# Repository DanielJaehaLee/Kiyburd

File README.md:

# Kiyburd

**Split 40% ortholinear diode-less mechanical keyboard**

Kiyburd is a split keyboard built around a 44-key ortholinear grid, direct-pin wiring (no diode matrix), and a pair of Raspberry Pi Picos talking over TRRS. The goal is a compact, stabilizer-free board that is easier to wire and firmware-tune than a conventional matrix keyboard, without giving up QMK features.

| | |
|---|---|
| **Form factor** | Split 40% · 22 keys per half · 44 keys total |
| **Grid** | Ortholinear 1u keys · no stabilized keys |
| **Scanning** | Direct GPIO (diode-less / matrix-less) |
| **MCU** | Raspberry Pi Pico (RP2040) × 2 |
| **Inter-half link** | TRRS (PJ-320A) · full-duplex USART |
| **Firmware** | [QMK](https://qmk.fm/) |
| **PCB** | Reversible |
| **Status** | PCB designed and ordered · QMK port working · case and Vial still open |

---

## Why this layout

Most 40% boards still carry a row/column matrix, diodes, and at least a few 2u keys that need stabilizers. Kiyburd drops those on purpose:

- **Split 40%** keeps the hands apart and the keymap small enough that layers do the work of a full-size board.
- **Ortholinear 1u grid** removes stagger and every stabilizer. Every switch is the same Cherry MX footprint.
- **Direct wiring** maps each switch to its own RP2040 GPIO. No diodes, no shared rows/columns, no ghosting to design around.
- **Reversible PCB** means one Gerber set builds both halves.

The default firmware keymap is QWERTY with three extra layers (function keys, numbers/arrows, symbols/nav). The files under `keyboard layout/` also document an experimental layered map with Hangul legends.

---

## Repository layout

```
Kiyburd/
├── Firmware/                 QMK keyboard definition
│   ├── config.h              RP2040 bootloader + USART pins
│   ├── info.json             Matrix pins, USB IDs, layout geometry
│   ├── kiyburd.h             LAYOUT() macro
│   ├── rules.mk              RP2040 + split keyboard
│   └── keymaps/default/      QWERTY + Lower / Raise / Raise2
├── PCB/Kiyburd/              KiCad 7/8 project
│   ├── Kiyburd.kicad_sch
│   ├── Kiyburd.kicad_pcb
│   └── production/           BOM, CPL, Gerbers (Kiyburd.zip)
└── keyboard layout/          Keyboard Layout Editor JSON / SVG / PNG
```

---

## Hardware

### Bill of materials (per half)

| Qty | Part | Notes |
|----:|------|--------|
| 1 | Raspberry Pi Pico (RP2040) | Socket or solder; USB-C or Micro-USB depending on Pico revision |
| 1 | PJ-320A TRRS jack | Inter-half serial + GND |
| 22 | Cherry MX compatible switches | 5-pin preferred; footprint is `SW_Cherry_MX_1.00u_PCB_reversible` |
| 22 | 1u keycaps | No 2u / no stabs |
| 1 | TRRS cable | Tip-ring-ring-sleeve; not a TRS headphone cable |

Build two halves. The PCB is reversible: the Pico and TRRS footprints are placed so the same board works as left or right.

### Direct-pin map

Each switch is wired to one GPIO. Left and right halves mirror each other.

**Left half**

| Row | Col 0 | Col 1 | Col 2 | Col 3 | Col 4 | Col 5 |
|-----|-------|-------|-------|-------|-------|-------|
| 0 | GP7 | GP6 | GP5 | GP4 | GP3 | GP2 |
| 1 | GP13 | GP12 | GP11 | GP10 | GP9 | GP8 |
| 2 | GP22 | GP26 | GP27 | GP28 | GP15 | GP14 |
| 3 | GP18 | — | — | GP19 | GP20 | GP21 |

**Right half**

| Row | Col 0 | Col 1 | Col 2 | Col 3 | Col 4 | Col 5 |
|-----|-------|-------|-------|-------|-------|-------|
| 0 | GP2 | GP3 | GP4 | GP5 | GP6 | GP7 |
| 1 | GP8 | GP9 | GP10 | GP11 | GP12 | GP13 |
| 2 | GP14 | GP15 | GP28 | GP27 | GP26 | GP22 |
| 3 | GP21 | GP20 | GP19 | — | — | GP18 |

Split serial is full-duplex USART on the Pico's vendor serial driver:

| Signal | Pin |
|--------|-----|
| TX | GP1 |
| RX | GP0 |

Handedness defaults to left-as-master. Uncomment `#define MASTER_RIGHT` in `Firmware/config.h` if the right half should own USB.

### Ordering the PCB

Gerbers and assembly files live in `PCB/Kiyburd/production/`:

- `Kiyburd.zip` — Gerber/drill package
- `bom.csv` — bill of materials
- `positions.csv` — pick-and-place
- `designators.csv` / `netlist.ipc`

Open `PCB/Kiyburd/Kiyburd.kicad_pro` in KiCad to edit the board before re-exporting.

---

## Firmware

Firmware is a QMK keyboard named `kiyburd`. It targets the RP2040 bootloader and enables Bootmagic, extra keys, mouse keys, and NKRO.

### Features (`info.json`)

- `bootmagic`, `extrakey`, `mousekey`, `nkro`
- USB VID `0xFEED` / PID `0x0000` / device version `1.0.0` (change these before sharing boards)
- Double-tap reset on the Pico (`RP2040_BOOTLOADER_DOUBLE_TAP_RESET`, 1000 ms window)

### Build

After [setting up QMK](https://docs.qmk.fm/#/newbs):

```sh
# drop this folder into qmk_firmware/keyboards/kiyburd
make kiyburd:default
make kiyburd:default:flash
```

Or with the QMK CLI:

```sh
qmk compile -kb kiyburd -km default
qmk flash -kb kiyburd -km default
```

Copy the contents of `Firmware/` to `qmk_firmware/keyboards/kiyburd/` so the make target matches the documented name.

### Enter the bootloader

1. **Bootmagic** — hold the matrix `(0, 0)` key (Tab on the default map) and plug in USB.
2. **Double-tap reset** — tap the Pico RESET button twice within one second.
3. **Bootsel** — hold BOOTSEL on the Pico, plug in USB, then drop the `.uf2` onto the RPI-RP2 drive.

### Default keymap

Four layers. Modifiers stay on the home row edges; `MO(1)` / `MO(2)` / `MO(3)` sit on the inner thumb cluster.

```
Layer 0 — QWERTY
,-----------------------------------------.     ,-----------------------------------------.
| Tab  |  Q   |  W   |  E   |  R   |  T   |     |  Y   |  U   |  I   |  O   |  P   | Bksp |
| Ctrl |  A   |  S   |  D   |  F   |  G   |     |  H   |  J   |  K   |  L   |  ;   |  '   |
| Shift|  Z   |  X   |  C   |  V   |  B   |     |  N   |  M   |  ,   |  .   |  /   |  \   |
| Alt  |           | GUI |Lower| Space |     |Raise|Raise2| RAlt |           | Enter|
`-----------------------------------------'     `-----------------------------------------'

Layer 1 — Lower          function keys on the right hand
Layer 2 — Raise          1–0, ` - = [ ], arrows
Layer 3 — Raise2         shifted symbols, Home / Ins / Del / End
```

Edit `Firmware/keymaps/default/keymap.c` to change layers. The Keyboard Layout Editor sources in `keyboard layout/` are a good place to mock a new map before touching C.

---

## Build notes

1. Fabricate two PCBs from `PCB/Kiyburd/production/Kiyburd.zip`.
2. Solder the Pico and TRRS jack. Because the footprints are reversible, decide handedness before soldering if you are not using sockets.
3. Solder 22 MX switches per half. There are no diodes.
4. Flash QMK to both Picos.
5. Join the halves with a TRRS cable. Plug USB into the master half only.
6. Confirm every key in a matrix tester, then cap the board.

There is no case in this repo yet. The housing work is still an open milestone (FreeCAD).

---

## Project status

| Area | State |
|------|--------|
| KiCad proficiency / PCB design | Done |
| PCB ordered | Done |
| Direct-switch and split-link electrical design | Done |
| QMK port | Done |
| Vial | Not started |
| Case / FreeCAD | Not started |

---

## References

Designs that informed the brief:

- [Budgy](https://github.com/doesntfazer/Budgy) — Pico-powered split, diode-less
- [Cantor](https://github.com/diepala/cantor) — 42-key diode-less split
- [Chiron](https://github.com/qmk/qmk_firmware/blob/master/keyboards/handwired/chiron/keymaps/default/keymap.c)
- [Dactyl Manuform](https://github.com/qmk/qmk_firmware/tree/master/keyboards/handwired/dactyl_manuform)

Docs:

- [QMK getting started](https://docs.qmk.fm/#/newbs)
- [QMK split keyboard](https://docs.qmk.fm/#/feature_split_keyboard)
- [RP2040 on QMK](https://docs.qmk.fm/#/platformdev_rp2040)

---

## License

Firmware sources carry `SPDX-License-Identifier: GPL-2.0-or-later` (QMK). Hardware files in `PCB/` do not declare a license yet — treat them as all-rights-reserved unless a license is added.

Maintainer: [DanielJaehaLee](https://github.com/DanielJaehaLee)

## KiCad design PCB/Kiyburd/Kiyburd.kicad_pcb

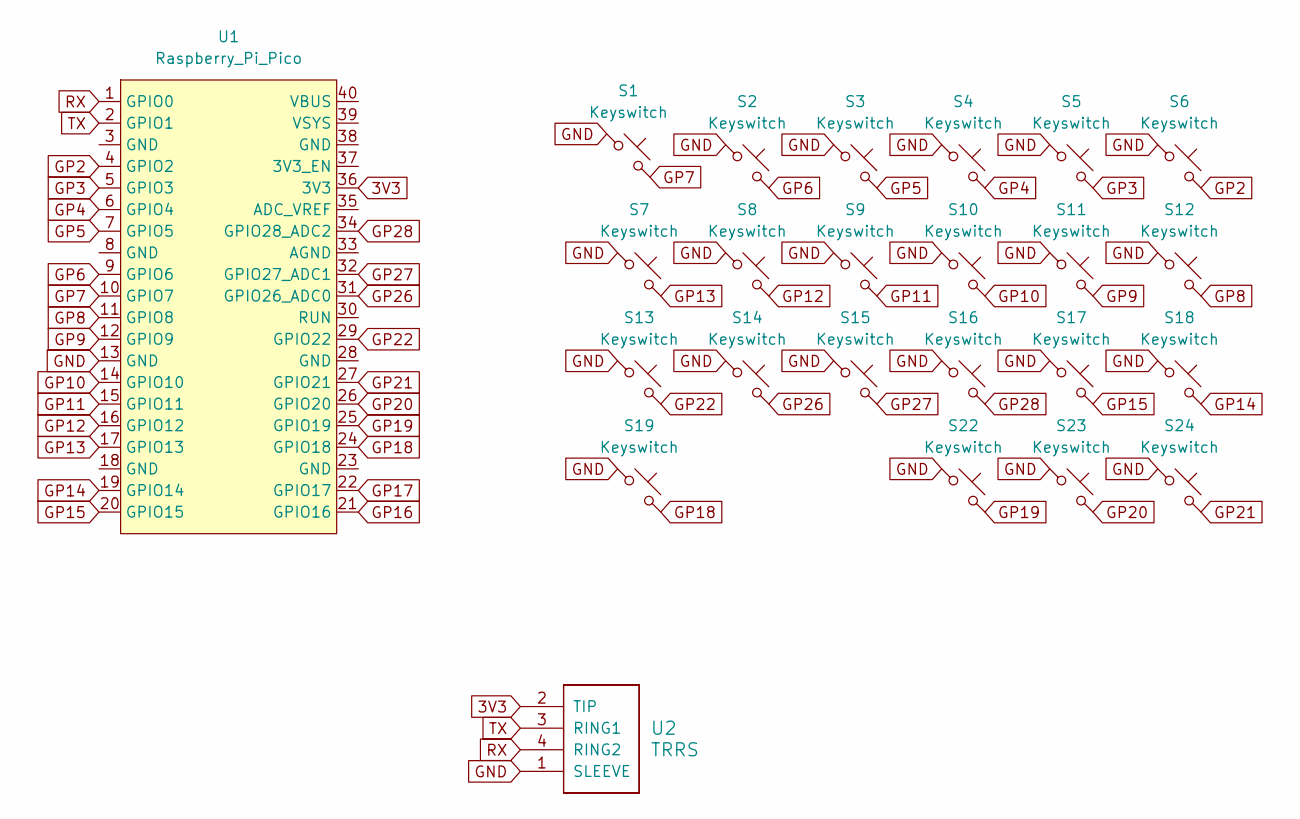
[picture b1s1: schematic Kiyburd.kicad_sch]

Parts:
S1, S2, S3, S4, S5, S6, S7, S8, S9, S10, S11, S12, S13, S14, S15, S16, S17, S18, S19, S22, S23, S24: Keyswitch; SW_Cherry_MX_1.00u_PCB_reversible
U1: Raspberry_Pi_Pico; Raspberry_Pi_Pico_reversible
U2: TRRS; PJ-320A_reversible

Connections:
3V3: U1.36 (3V3), U2.2 (TIP)
GND: S1.1, S2.1, S3.1, S4.1, S5.1, S6.1, S7.1, S8.1, S9.1, S10.1, S11.1, S12.1, S13.1, S14.1, S15.1, S16.1, S17.1, S18.1, S19.1, S22.1, S23.1, S24.1, U1.13 (GND), U2.1 (SLEEVE)
GP2: S6.2, U1.4 (GPIO2)
GP3: S5.2, U1.5 (GPIO3)
GP4: S4.2, U1.6 (GPIO4)
GP5: S3.2, U1.7 (GPIO5)
GP6: S2.2, U1.9 (GPIO6)
GP7: S1.2, U1.10 (GPIO7)
GP8: S12.2, U1.11 (GPIO8)
GP9: S11.2, U1.12 (GPIO9)
GP10: S10.2, U1.14 (GPIO10)
GP11: S9.2, U1.15 (GPIO11)
GP12: S8.2, U1.16 (GPIO12)
GP13: S7.2, U1.17 (GPIO13)
GP14: S18.2, U1.19 (GPIO14)
GP15: S17.2, U1.20 (GPIO15)
GP16: U1.21 (GPIO16)
GP17: U1.22 (GPIO17)
GP18: S19.2, U1.24 (GPIO18)
GP19: S22.2, U1.25 (GPIO19)
GP20: S23.2, U1.26 (GPIO20)
GP21: S24.2, U1.27 (GPIO21)
GP22: S13.2, U1.29 (GPIO22)
GP26: S14.2, U1.31 (GPIO26_ADC0)
GP27: S15.2, U1.32 (GPIO27_ADC1)
GP28: S16.2, U1.34 (GPIO28_ADC2)
RX: U1.1 (GPIO0), U2.4 (RING2)
TX: U1.2 (GPIO1), U2.3 (RING1)

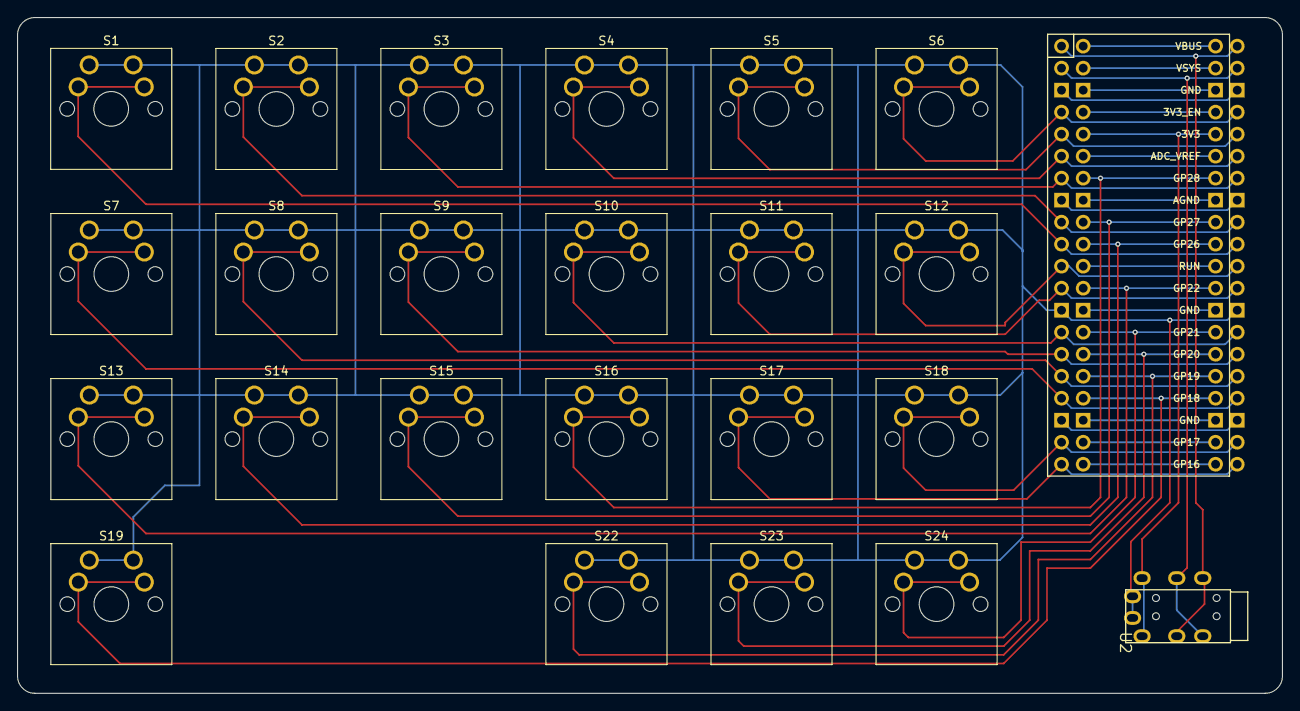
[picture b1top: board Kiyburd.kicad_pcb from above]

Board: 2 copper layers, 146.0 x 78.0 mm, 24 parts (0 on the bottom side), 26 nets.

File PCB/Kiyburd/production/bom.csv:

Designator,Footprint,Quantity,Value,LCSC Part #
"S1, S10, S11, S12, S13, S14, S15, S16, S17, S18, S19, S2, S22, S23, S24, S3, S4, S5, S6, S7, S8, S9",SW_Cherry_MX_1.00u_PCB_reversible,22,Keyswitch,
U1,Raspberry_Pi_Pico_reversible,1,Raspberry_Pi_Pico,
U2,PJ-320A_reversible,1,TRRS,

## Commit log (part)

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2024-05-08 feat(firmware)
    firmware made through Keyboard Firmwar Builder
2024-05-10 Backup
    Keyboard Layout & QMK firmwar
2024-05-12 feat(PCB)
    PCB designed
    PROTOTYPE v.01
2024-07-30 Finalize
